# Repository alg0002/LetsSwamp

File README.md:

# Let's Swamp

<!--  -->

DIY keyboard "Let's Swamp"

---

## ⌨️What is "Let's Swamp" ?

Let's Swamp is an ortholinear split keyboard.

 * 4x6x2=48keys
 * Controller board : Waveshare RP2040-Zero
 * Supported firmware :
    - [Kermite](https://kermite.org/)
    - [PRK Firmware](https://github.com/picoruby/prk_firmware)
    - [QMK Firmware](https://docs.qmk.fm/#/)

---

## 📃License

 * KiCad design files (in [`design`](./design/) directory) : MIT
 * Firmware files (in [`firmware`](./firmware/) directory) : MIT
 * Gerber files (in `gerber` directory)  : MIT
 * Other files: MIT
 
I have modified [Salicylic-acid3/KiCAD_FootPrint](https://github.com/Salicylic-acid3/KiCAD_FootPrint) to use in this project.

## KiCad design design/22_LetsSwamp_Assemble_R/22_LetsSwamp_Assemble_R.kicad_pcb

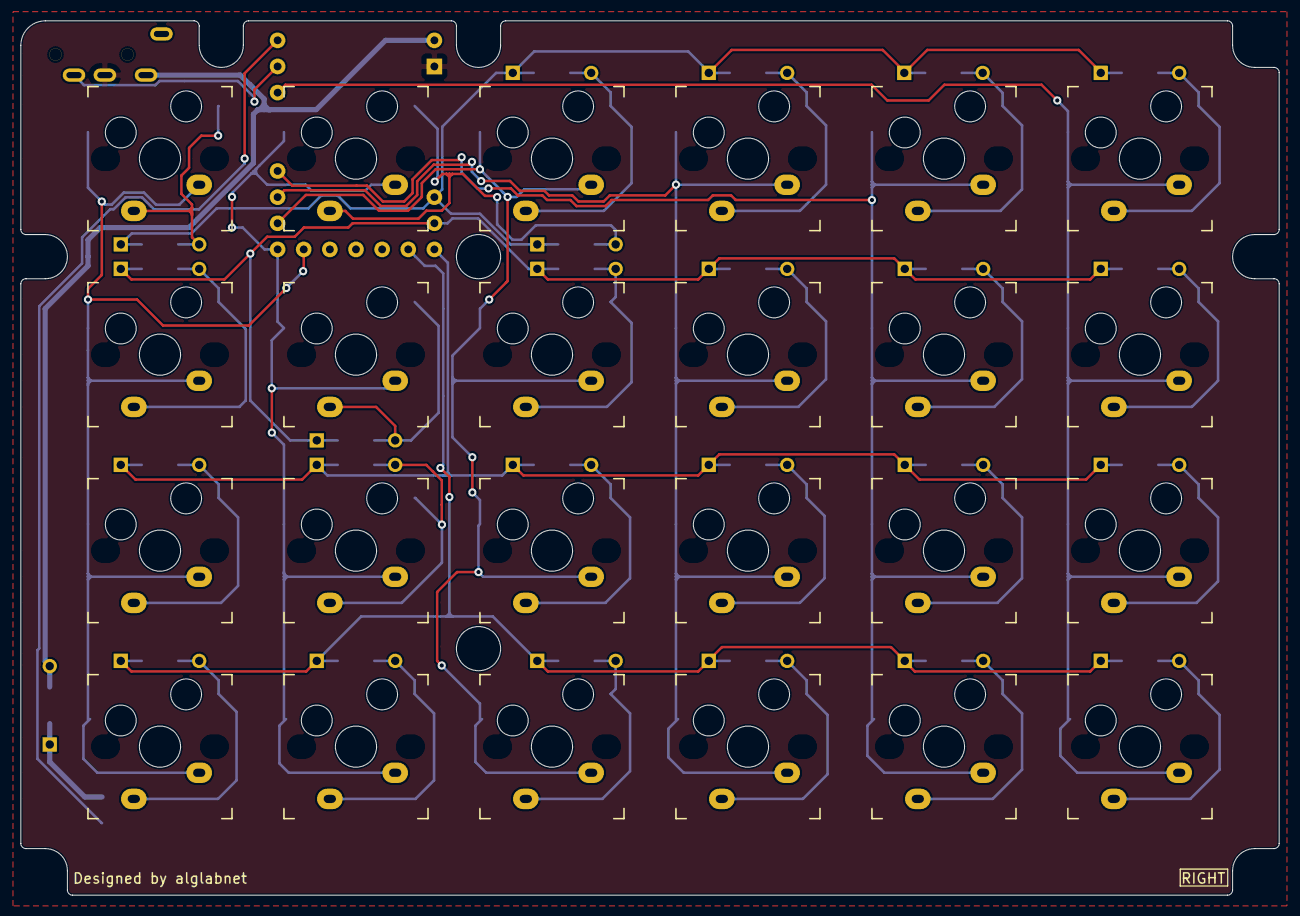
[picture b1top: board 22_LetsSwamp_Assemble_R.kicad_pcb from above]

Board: 2 copper layers, 122.3 x 85.0 mm, 52 parts (1 on the bottom side), 39 nets.

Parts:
D25, D26, D27, D28, D29, D30, D31, D32, D33, D34, D35, D36, D37, D38, D39, D40, D41, D42, D43, D44, D45, D46, D47, D48, D50: D; Diode_TH_SMD
J1: MJ-4PP-9; TRRS_MJ-4PP-9
J2: Conn_01x03; LED_Tape
SW25, SW26, SW27, SW28, SW29, SW30, SW31, SW32, SW33, SW34, SW35, SW36, SW37, SW38, SW39, SW40, SW41, SW42, SW43, SW44, SW45, SW46, SW47, SW48: SW_Push; CherryMX_HotswapAndSolder_1u
U1: Waveshare_RP2040-Zero; Waveshare_RP2040-Zero_Reverse_OmitPins

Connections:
COL0: SW25.1, SW26.1, SW27.1, SW28.1, U1.14
COL1: SW29.1, SW30.1, SW31.1, SW32.1, U1.15
COL2: SW33.1, SW34.1, SW35.1, SW36.1, U1.16
COL3: SW37.1, SW38.1, SW39.1, SW40.1, U1.17
COL4: SW41.1, SW42.1, SW43.1, SW44.1, U1.18
COL5: SW45.1, SW46.1, SW47.1, SW48.1, U1.21
DATA: J1.B, U1.22
GND: J1.C, J2.1, U1.2
LED: J2.2, U1.23
unnamed: D25.2, SW25.2
unnamed: D26.2, SW26.2
unnamed: D27.2, SW27.2
unnamed: D28.2, SW28.2
unnamed: D29.2, SW29.2
unnamed: D30.2, SW30.2
unnamed: D31.2, SW31.2
unnamed: D32.2, SW32.2
unnamed: D33.2, SW33.2
unnamed: D34.2, SW34.2
unnamed: D35.2, SW35.2
unnamed: D36.2, SW36.2
unnamed: D37.2, SW37.2
unnamed: D38.2, SW38.2
unnamed: D39.2, SW39.2
unnamed: D40.2, SW40.2
unnamed: D41.2, SW41.2
unnamed: D42.2, SW42.2
unnamed: D43.2, SW43.2
unnamed: D44.2, SW44.2
unnamed: D45.2, SW45.2
unnamed: D46.2, SW46.2
unnamed: D47.2, SW47.2
unnamed: D48.2, SW48.2
unnamed: D50.1, J2.3
ROW0: D25.1, D29.1, D33.1, D37.1, D41.1, D45.1, U1.7
ROW1: D26.1, D30.1, D34.1, D38.1, D42.1, D46.1, U1.8
ROW2: D27.1, D31.1, D35.1, D39.1, D43.1, D47.1, U1.9
ROW3: D28.1, D32.1, D36.1, D40.1, D44.1, D48.1, U1.10
VCC: D50.2, J1.D, U1.1

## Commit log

2023-01-02 v0.3
2023-01-03 Move kicad files
2023-01-03 Add LICENSE and README.md
2023-01-05 Modify middle plates
    avoid to pin sockets and some diodes
2023-01-05 Modify reference number
2023-01-07 Change to order
2023-01-09 Add kana name
2023-01-15 Add firmware directory
2023-01-15 about firmware in readme
2023-01-17 Change middle plates for the diode to the LED tape
2023-01-17 Change diodes footprint
2023-01-23 Hide JLCJLCJLC
2023-02-02 v1.0(JLCPCB)
2023-02-04 Add data for order
2023-03-23 Modify .gitignore fore KiCad 7
2023-03-23 Add document (ja)
2023-04-02 Modify document (ja)
2023-04-02 Modify README
    * Version Number
    * License

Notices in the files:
README.md:
KiCAD design License:MIT
Gerber:CC-BY-NC
